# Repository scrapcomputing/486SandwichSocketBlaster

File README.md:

# 486 Sandwich Socket Blaster

The 486 Sandwich Socket Blaster is an alternative design for the [486SocketBlaster](https://github.com/scrapcomputing/486SocketBlaster) that is much easier to solder and put together.
It is a simple voltage adapter / interposer for 486 processors that allows you to use a 3-volt 486 CPU on an older 5-volt-only motherboard.
For example you can use a DX4 or an Am5x86 on an old 486 motherboard that would normally only work with 5-volt CPUs.
This basically converts any 3-volt CPU to an "Overdrive".

> [Warning!]
> This design is *VERY* experimental and is unstable when used with some motherboards. You have been warned!

# How does it work ?

It is really simple: All CPU pins are passed through to the motherboard socket, except for the Vcc.
Those are connected to the output of a the on-board voltage regulator or a mini buck converter that can be soldered to the board.

# Videos

- https://www.youtube.com/watch?v=dKPT36-fnws

# Soldering/Assembly Instructions

The adapter includes two parts: the top and bottom part, both of which use the exact same PCB.
The two parts connect to each other with standard 2.54mm-pitch pin-headers, the top part with male headers and the bottom part with female headers.
The top part accepts the CPU with either a female 168-pin BGA socket, or an equivalent collection of female headers.
The bottom part is for the pins that insert into the motherboard socket.
The pins are made of widely available pin-headers.

## Solder Jumpers
These need to be set differently for the top and bottom parts (see silk-screen).

# Voltage regulator

The Sandwich Socket Blaster can be powered by a regulator circuit that can be soldered to the board based on the AP7176B chip, or by an of-the-shelf mini buck converter.
Unlike the original Socket Blaster, this only accepts the small voltage buck converter (18mm x 12mm), usually found using keywords like "mini buck converter".
These are commonly rated at up to 3A of current.
Given that 3-volt 486 CPUs are usually very efficient (the DX4-100 is rated at max 3.55/5.22W typical/max) such a regulator should be adequate in most cases.
For best stability try to source a good quality part.

If you are planning to overclock or to use a more power hungry CPU, please use an external regulation circuit plugged in to the `EXTPWR` header, or use a *very* good quality mini buck converter.

# WARNING!!!

Please make sure you know what you are doing!
Improper assembly/settings/use can damage both your precious motherboard and your precious CPU!

# Features

- You can choose between an soldered-on linear regulator circuit or a mini buck converter.
- External Power Header. This can be used either for monitoring the CPU voltage, or for providing power externally, either with an external power supply or an external voltage regulator.
- CLKMUL Header for selecting/overriding the CPU multiplier. This controls CPU pin `R17`. 1-2 connects it to the motherboard socket pin and 2-3 connects it to ground. This reduces the multiplier of a DX4 to 2x (66MHz) and sets the multiplier of an Am5x86 to 4x (133MHz).
- WB/WT Header for selecting/overriding Write-Back/Write-Through cache. This controls processor CPU pin `B13` (which is the `CLKMUL` pin in earlier 486 CPUs). 1-2 connects it to the motherboard socket pin, and 2-3 connects it to Vcc, which enables Write-Back.
- STPCLK pin for use with the Throttle Blaster. This connects directly to CPU pin `G15`, which in DX4 and 5x86 CPUs is the STPCLK pin. This allows you to throttle down the CPU and achieve the whole range of speeds from the original IBM PC all the way to the max speed the CPU can provide.

# Bill of materials

Item                                               | ##  | Description
---------------------------------------------------|-----|--------------------------------------------------------
486 Sandwich Socket Blaster PCB                    | 2   | We need 2 identical boards, one for the top and one for the bottom.
mini buck converter (or AP7176B)                   | 1   | We only the small 18mm x 12mm ones. These usually have chips like MP1584, MP2307 and others
AP7176B MSOP-8EP 3.3mm P0.65mm (or mini buck)      | 1   | Modern linear voltage regulator, alternative to the mini buck converter
SMD Ceramic capacitor 10uf 10+V 1206 (for AP7176B) | 2   | To be used with the AP7176B regulator
SMD Ceramic capacitor  1uf 10+V 1206 (for AP7176B) | 1   | To be used with the AP7176B regulator
SMD Ceramic capacitor 10uf 10+V 1206               | 4   | For CPU pin voltage stability
2x11 female pin-header 2.54mm pitch                | 2   | Connects top/bottom PCBs
2x11 male pin-header 2.54mm pitch                  | 2   | Connects top/bottom PCBs
2x6 female pin-header 2.54mm pitch                 | 2   | Connects top/bottom PCBs
2x6 male pin-header 2.54mm pitch                   | 2   | Connects top/bottom PCBs
1x16 female pin-header 2.54mm pitch                | 2   | Connects top/bottom PCBs
1x16 male pin-header 2.54mm pitch                  | 2   | Connects top/bottom PCBs
1x19 female pin-header 2.54mm pitch                | 1   | Connects top/bottom PCBs
1x19 male pin-header 2.54mm pitch                  | 1   | Connects top/bottom PCBs
1x18 female pin-header 2.54mm pitch                | 1   | Connects top/bottom PCBs
1x18 male pin-header 2.54mm pitch                  | 1   | Connects top/bottom PCBs
40pin SIP pin header (male)                        | 5   | Single-row round (machined) pin 2.54mm pitch (male). Socket pin diameter: 0.50mm (see photo below)
40pin SIP socket header (female)                   | 5   | Single-row round (machined) pin sockets, 2.54mm pitch (see photo below) 
3-pin header 2.54mm pitch                          | 2   | (optional) Headers for CLKMUL, WB/WT
2-pin header 2.54mm pitch                          | 1   | (optional) Header for STPCLK
1-pin header 2.54mm pitch                          | 1   | (optional) For connecting the Throttle Blaster to STPCLK.
Jumper 2.54mm pitch                                | 2   | (optional) Jumpers for the CLKMUL and WB/WT headers

Gerber files can be found in the releases: https://github.com/scrapcomputing/486SandwichSocketBlaster/releases

Please note that the headers used for the socket pins (bottom board) are a very tight fit. So please make sure that you get headers of the correct pin diameter.

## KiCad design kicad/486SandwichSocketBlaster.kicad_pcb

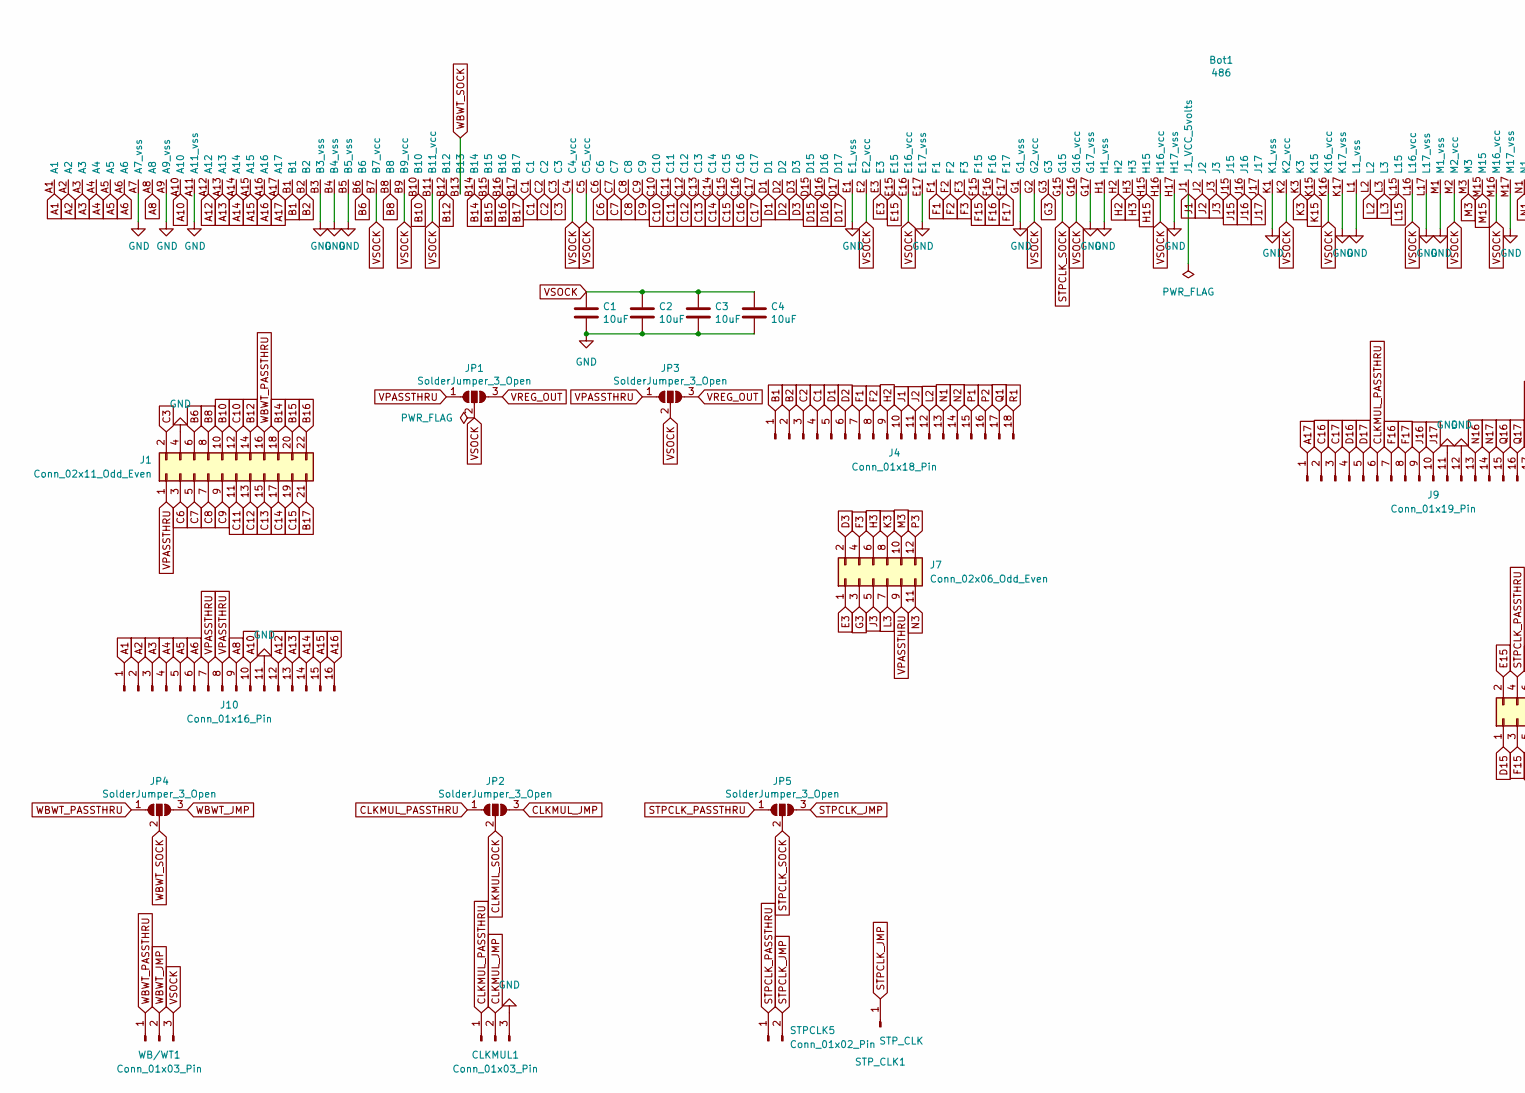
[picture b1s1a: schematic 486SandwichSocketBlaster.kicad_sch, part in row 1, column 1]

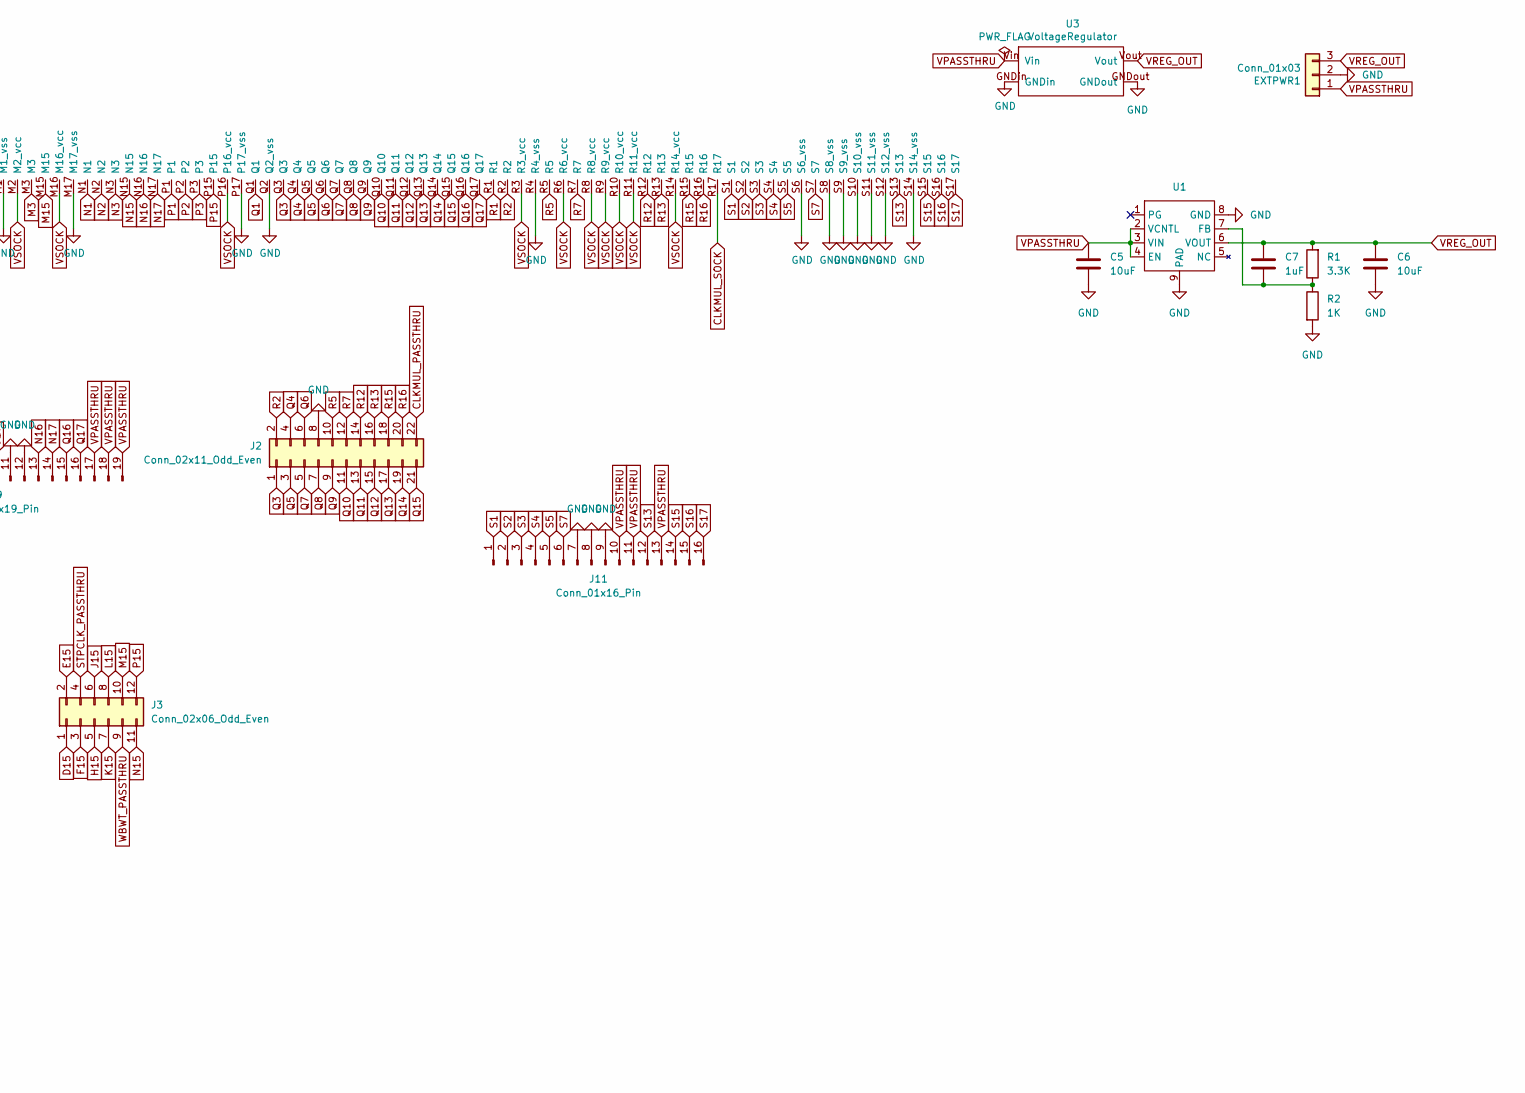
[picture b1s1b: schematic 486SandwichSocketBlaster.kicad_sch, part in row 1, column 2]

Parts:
Bot1: 486; 486_168pga_socket
C1, C2, C3, C4, C5, C6: 10uF; C_1206_3216Metric_Pad1.33x1.80mm_HandSolder
C7: 1uF; C_1206_3216Metric_Pad1.33x1.80mm_HandSolder
CLKMUL1: Conn_01x03_Pin; PinHeader_1x03_P2.54mm_Vertical
EXTPWR1: Conn_01x03; PinHeader_1x03_P2.54mm_Vertical
J1, J2: Conn_02x11_Odd_Even; PinHeader_2x11_P2.54mm_Vertical
J3, J7: Conn_02x06_Odd_Even; PinHeader_2x06_P2.54mm_Vertical
J4: Conn_01x18_Pin; PinHeader_1x18_P2.54mm_Vertical
J9: Conn_01x19_Pin; PinHeader_1x19_P2.54mm_Vertical
J10, J11: Conn_01x16_Pin; PinHeader_1x16_P2.54mm_Vertical
JP1, JP2, JP3, JP4, JP5: SolderJumper_3_Open; SolderJumper-3_P1.3mm_Open_Pad1.0x1.5mm_NumberLabels
R1: 3.3K; R_1206_3216Metric_Pad1.30x1.75mm_HandSolder
R2: 1K; R_1206_3216Metric_Pad1.30x1.75mm_HandSolder
STPCLK5: Conn_01x02_Pin; PinHeader_1x02_P2.54mm_Vertical
STP_CLK1: STP_CLK; PinHeader_1x01_P2.54mm_Vertical
U1: MSOP-8-1EP_3x3mm_P0.65mm_EP1.95x2.15mm_ThermalVias
U3: VoltageRegulator
WB/WT1: Conn_01x03_Pin; PinHeader_1x03_P2.54mm_Vertical

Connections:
A1: Bot1.A1, J10.1
A2: Bot1.A2, J10.2
A3: Bot1.A3, J10.3
A4: Bot1.A4, J10.4
A5: Bot1.A5, J10.5
A6: Bot1.A6, J10.6
A8: Bot1.A8, J10.9
A10: Bot1.A10, J10.10
A12: Bot1.A12, J10.12
A13: Bot1.A13, J10.13
A14: Bot1.A14, J10.14
A15: Bot1.A15, J10.15
A16: Bot1.A16, J10.16
A17: Bot1.A17, J9.1
B1: Bot1.B1, J4.1
B2: Bot1.B2, J4.2
B6: Bot1.B6, J1.6
B8: Bot1.B8, J1.8
B10: Bot1.B10, J1.10
B12: Bot1.B12, J1.14
B14: Bot1.B14, J1.18
B15: Bot1.B15, J1.20
B16: Bot1.B16, J1.22
B17: Bot1.B17, J1.21
C1: Bot1.C1, J4.4
C2: Bot1.C2, J4.3
C3: Bot1.C3, J1.2
C6: Bot1.C6, J1.3
C7: Bot1.C7, J1.5
C8: Bot1.C8, J1.7
C9: Bot1.C9, J1.9
C10: Bot1.C10, J1.12
C11: Bot1.C11, J1.11
C12: Bot1.C12, J1.13
C13: Bot1.C13, J1.15
C14: Bot1.C14, J1.17
C15: Bot1.C15, J1.19
C16: Bot1.C16, J9.2
C17: Bot1.C17, J9.3
CLKMUL_JMP: CLKMUL1.2, JP2.3 (B)
CLKMUL_PASSTHRU: CLKMUL1.1, J2.22, J9.6, JP2.1 (A)
CLKMUL_SOCK: Bot1.R17, JP2.2 (C)
D1: Bot1.D1, J4.5
D2: Bot1.D2, J4.6
D3: Bot1.D3, J7.2
D15: Bot1.D15, J3.1
D16: Bot1.D16, J9.4
D17: Bot1.D17, J9.5
E3: Bot1.E3, J7.1
E15: Bot1.E15, J3.2
F1: Bot1.F1, J4.7
F2: Bot1.F2, J4.8
F3: Bot1.F3, J7.4
F15: Bot1.F15, J3.3
F16: Bot1.F16, J9.7
F17: Bot1.F17, J9.8
G3: Bot1.G3, J7.3
GND: Bot1.A7 (A7_vss), Bot1.A9 (A9_vss), Bot1.A11 (A11_vss), Bot1.B3 (B3_vss), Bot1.B4 (B4_vss), Bot1.B5 (B5_vss), Bot1.E1 (E1_vss), Bot1.E17 (E17_vss), Bot1.G1 (G1_vss), Bot1.G17 (G17_vss), Bot1.H1 (H1_vss), Bot1.H17 (H17_vss), Bot1.K1 (K1_vss), Bot1.K17 (K17_vss), Bot1.L1 (L1_vss), Bot1.L17 (L17_vss), Bot1.M1 (M1_vss), Bot1.M17 (M17_vss), Bot1.P17 (P17_vss), Bot1.Q2 (Q2_vss), Bot1.R4 (R4_vss), Bot1.S6 (S6_vss), Bot1.S8 (S8_vss), Bot1.S9 (S9_vss), Bot1.S10 (S10_vss), Bot1.S11 (S11_vss), Bot1.S12 (S12_vss), Bot1.S14 (S14_vss), C1.2, C2.2, C3.2, C4.2, C5.2, C6.2, CLKMUL1.3, EXTPWR1.2, J1.4, J2.8, J9.11, J9.12, J10.11, J11.7, J11.8, J11.9, R2.2, U1.8 (GND), U1.9 (PAD), U3.GNDin, U3.GNDout
H2: Bot1.H2, J4.9
H3: Bot1.H3, J7.6
H15: Bot1.H15, J3.5
J1: Bot1.J1 (J1_VCC_5volts), J4.10
J2: Bot1.J2, J4.11
J3: Bot1.J3, J7.5
J15: Bot1.J15, J3.6
J16: Bot1.J16, J9.9
J17: Bot1.J17, J9.10
K3: Bot1.K3, J7.8
K15: Bot1.K15, J3.7
L2: Bot1.L2, J4.12
L3: Bot1.L3, J7.7
L15: Bot1.L15, J3.8
M3: Bot1.M3, J7.10
M15: Bot1.M15, J3.10
N1: Bot1.N1, J4.13
N2: Bot1.N2, J4.14
N3: Bot1.N3, J7.11
N15: Bot1.N15, J3.11
N16: Bot1.N16, J9.13
N17: Bot1.N17, J9.14
unnamed: C7.2, R1.1, R2.1, U1.7 (FB)
P1: Bot1.P1, J4.15
P2: Bot1.P2, J4.16
P3: Bot1.P3, J7.12
P15: Bot1.P15, J3.12
Q1: Bot1.Q1, J4.17
Q3: Bot1.Q3, J2.1
Q4: Bot1.Q4, J2.4
Q5: Bot1.Q5, J2.3
Q6: Bot1.Q6, J2.6
Q7: Bot1.Q7, J2.5
Q8: Bot1.Q8, J2.7
Q9: Bot1.Q9, J2.9
Q10: Bot1.Q10, J2.11
Q11: Bot1.Q11, J2.13
Q12: Bot1.Q12, J2.15
Q13: Bot1.Q13, J2.17
Q14: Bot1.Q14, J2.19
Q15: Bot1.Q15, J2.21
Q16: Bot1.Q16, J9.15
Q17: Bot1.Q17, J9.16
R1: Bot1.R1, J4.18
R2: Bot1.R2, J2.2
R5: Bot1.R5, J2.10
R7: Bot1.R7, J2.12
R12: Bot1.R12, J2.14
R13: Bot1.R13, J2.16
R15: Bot1.R15, J2.18
R16: Bot1.R16, J2.20
S1: Bot1.S1, J11.1
S2: Bot1.S2, J11.2
S3: Bot1.S3, J11.3
S4: Bot1.S4, J11.4
S5: Bot1.S5, J11.5
S7: Bot1.S7, J11.6
S13: Bot1.S13, J11.12
S15: Bot1.S15, J11.14
S16: Bot1.S16, J11.15
S17: Bot1.S17, J11.16
STPCLK_JMP: JP5.3 (B), STPCLK5.2, STP_CLK1.1
STPCLK_PASSTHRU: J3.4, JP5.1 (A), STPCLK5.1
STPCLK_SOCK: Bot1.G15, JP5.2 (C)
VPASSTHRU: C5.1, EXTPWR1.1, J1.1, J7.9, J9.17, J9.18, J9.19, J10.7, J10.8, J11.10, J11.11, J11.13, JP1.1 (A), JP3.1 (A), U1.2 (VCNTL), U1.3 (VIN), U1.4 (EN), U3.Vin
VREG_OUT: C6.1, C7.1, EXTPWR1.3, JP1.3 (B), JP3.3 (B), R1.2, U1.6 (VOUT), U3.Vout
VSOCK: Bot1.B7 (B7_vcc), Bot1.B9 (B9_vcc), Bot1.B11 (B11_vcc), Bot1.C4 (C4_vcc), Bot1.C5 (C5_vcc), Bot1.E2 (E2_vcc), Bot1.E16 (E16_vcc), Bot1.G2 (G2_vcc), Bot1.G16 (G16_vcc), Bot1.H16 (H16_vcc), Bot1.K2 (K2_vcc), Bot1.K16 (K16_vcc), Bot1.L16 (L16_vcc), Bot1.M2 (M2_vcc), Bot1.M16 (M16_vcc), Bot1.P16 (P16_vcc), Bot1.R3 (R3_vcc), Bot1.R6 (R6_vcc), Bot1.R8 (R8_vcc), Bot1.R9 (R9_vcc), Bot1.R10 (R10_vcc), Bot1.R11 (R11_vcc), Bot1.R14 (R14_vcc), C1.1, C2.1, C3.1, C4.1, JP1.2 (C), JP3.2 (C), WB/WT1.3
WBWT_JMP: JP4.3 (B), WB/WT1.2
WBWT_PASSTHRU: J1.16, J3.9, JP4.1 (A), WB/WT1.1
WBWT_SOCK: Bot1.B13, JP4.2 (C)

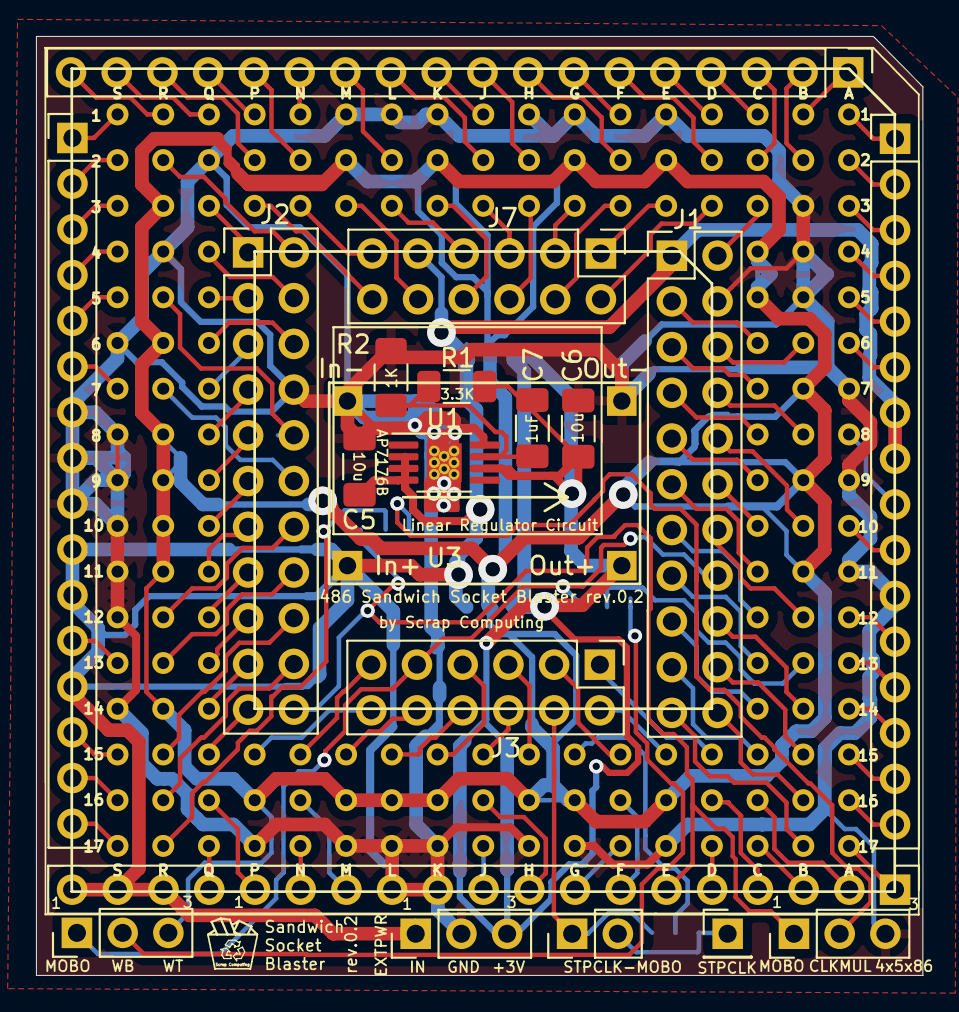
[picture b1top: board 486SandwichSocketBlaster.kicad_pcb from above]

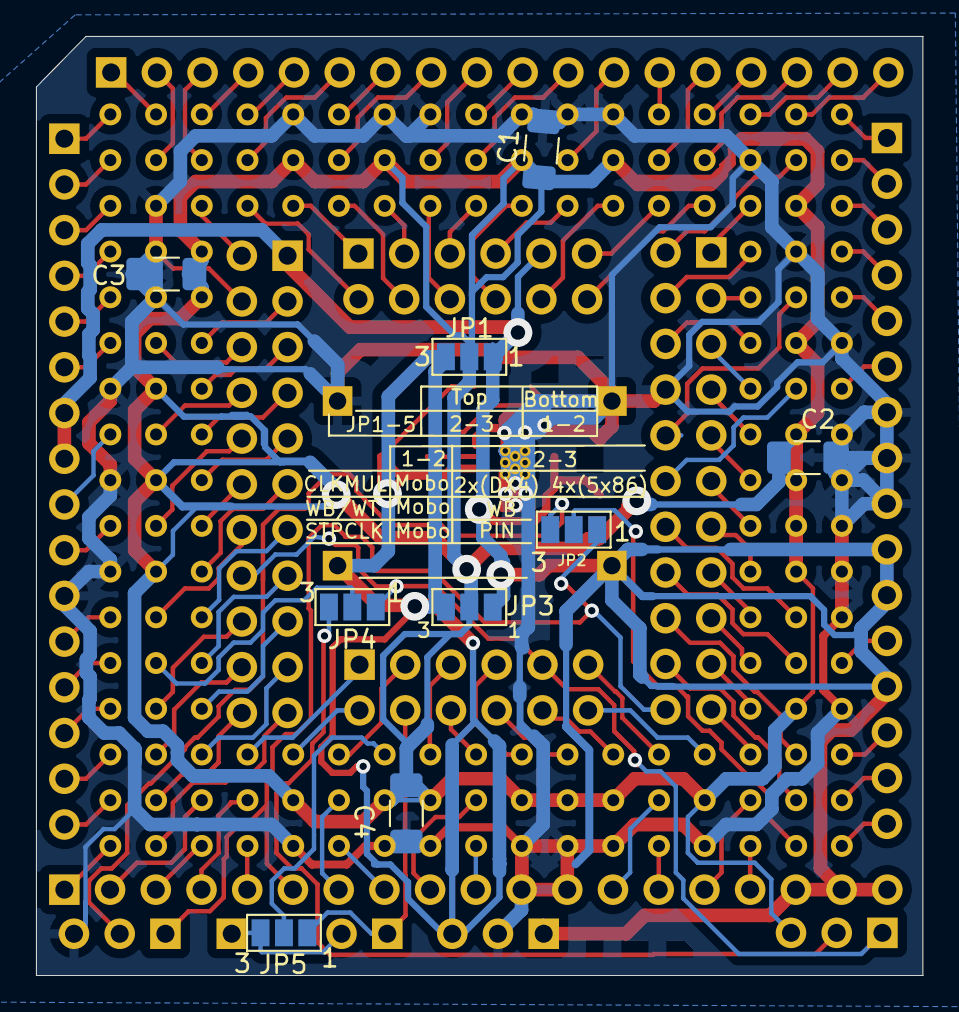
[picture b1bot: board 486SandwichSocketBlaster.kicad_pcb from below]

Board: 2 copper layers, 49.2 x 52.2 mm, 30 parts (9 on the bottom side), 128 nets.

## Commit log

2024-11-02 Rev.0.2
2024-11-03 README: Add link to video.
